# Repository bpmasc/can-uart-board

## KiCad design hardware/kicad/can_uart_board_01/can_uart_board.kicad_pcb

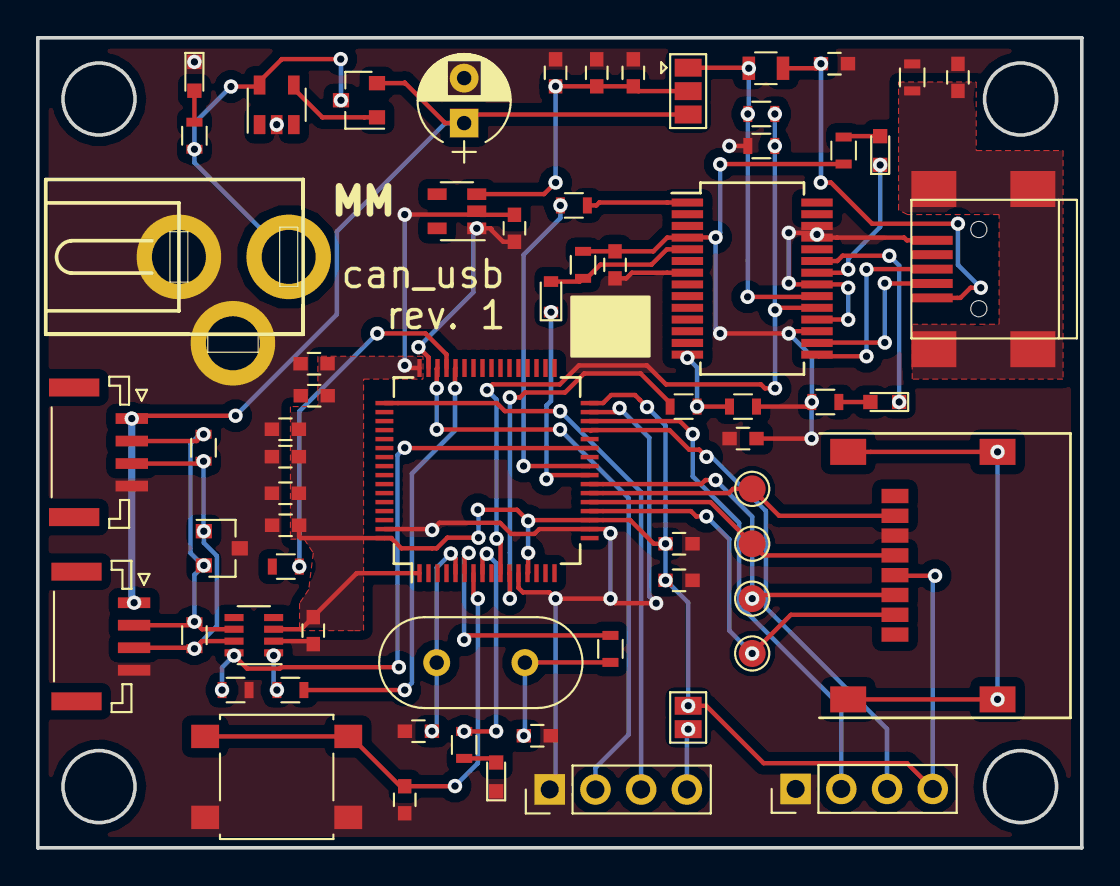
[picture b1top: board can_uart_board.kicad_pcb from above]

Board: 2 copper layers, 58.0 x 45.0 mm, 66 parts (0 on the bottom side), 46 nets.

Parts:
C10, C11: C; C_0603
C12, C13, C15, C40: 0.1u; C_0603
C14, C16, C28, C200: 4.7u; C_0603
C17: 0.01u; C_0603
C19: CP; CP_Radial_D5.0mm_P2.50mm
C20, C25, C26, C27, C29, C201: 100n; C_0603
C23, C24: 20p; C_0603
C202: 1u; C_0603
D10: D_Zener; D_0603
D11, D12, D13, D20: LED; LED_0603
D40: NUP2105L; SOT-23
FB0: Ferrite_Bead; L_0805
J11: USB_B_Mini; USB_Mini-B
J12: Barrel_Jack_Switch; con-jack-DCJ0303
J20, J21: Conn_01x04_Male; Pin_Header_Straight_1x04_Pitch2.54mm
J30: Micro_SD_Card_Det; MicroSd_Wurth_693072010801
J40, J41: Conn_01x04_Male; JST_GH_SM04B-GHS-TB_04x1.25mm_Angled
JP0: Jumper_2_Open; SolderJumper-2_P1.3mm_Open_Pad1.0x1.5mm
JP10: Jumper_3_Open; SolderJumper-3_P1.3mm_Open_Pad1.0x1.5mm
Q10: CPH3462_SOT23_3; SOT-23
R10: 1M; R_0603
R11: 4k7; R_0603
R12, R14, R17, R18: 10k; R_0603
R13, R26, R27, R42, R43: 0; R_0603
R15, R16, R19, R40, R44: 120; R_0603
R41: R; R_0603
SW20: SW_Push_Dual; SW_SPST_B3S-1000
TP30, TP31, TP32, TP33: TestPoint; TestPoint_Pad_D1.5mm
U10: FT232RL; SSOP-28_5.3x10.2mm_Pitch0.65mm
U11: TLV1117_33_SOT223; SOT-23-5
U13: TPS2400_SOT23_5; SOT-23-5
U40: MAX3051; SOT-23-8
U^20: STM32F091RBTx; LQFP-64_10x10mm_Pitch0.5mm
Y20: Crystal; Crystal_HC18-U_Vertical

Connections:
+3V3: C11.1, C25.1, C26.1, C27.1, C28.1, C29.1, C40.1, C200.1, C201.1, C202.1, J21.4, J30.4, JP0.1, U11.2, U40.3, U^20.1, U^20.13, U^20.19, U^20.32, U^20.48, U^20.64
/if_can/CAN_H: D40.1, J40.3, J41.3, R40.1, R44.1, U40.7
/if_can/CAN_L: D40.2, J40.2, J41.2, R40.2, R44.2, U40.6
/if_can/CAN_RS: R41.1, U40.8, U^20.27
/if_can/CAN_RX: R43.2, U^20.45
/if_can/CAN_TX: R42.2, U^20.44
/if_openlog/uSD_CS: J30.2, TP30.1, U^20.20
/if_openlog/uSD_MISO: J30.7, TP33.1, U^20.22
/if_openlog/uSD_MOSI: J30.3, TP31.1, U^20.23
/if_openlog/uSD_SCK: J30.5, TP32.1, U^20.21
/if_uart_power/CONV_N_USB: R18.2, U^20.11
/if_uart_power/FT232_3V3: C13.1, C14.1, R14.1, R15.1, R16.1, R17.1, U10.4, U10.17
/if_uart_power/FT232_DM: J11.2, U10.16
/if_uart_power/FT232_DP: J11.3, U10.15
/if_uart_power/UART_N_RESET: R11.2, R12.1, U10.19, U^20.10
/if_uart_power/UART_PW_EN: R17.2, R18.1, U10.14
/if_uart_power/UART_RX: R13.1, U^20.25
/if_uart_power/UART_RXLED: D12.1, U10.23
/if_uart_power/UART_TX: D10.1, U^20.24
/if_uart_power/UART_TXLED: D11.1, U10.22
/if_uart_power/USB_UART_VBUS: FB0.1, JP10.1, R11.1, U10.20
/if_uart_power/V_JUMPER: C10.1, C15.1, C16.1, JP10.2, U11.3
/uC/EXT_SCL: J21.3, U^20.29
/uC/EXT_SDA: J21.2, U^20.30
/uC/LED: R27.2, U^20.8
/uC/OSC_IN: C23.1, U^20.5, Y20.1
/uC/OSC_OUT: R26.1, U^20.6
/uC/SWCLK: J20.3, U^20.49
/uC/SWDIO: J20.2, U^20.46
/uC/nRESET: C20.1, SW20.2, U^20.7
GND: C10.2, C11.2, C12.2, C13.2, C14.2, C15.2, C16.2, C17.2, C19.2, C20.2, C23.2, C24.2, C25.2, C26.2, C27.2, C28.2, C29.2, C40.2, C200.2, C201.2, C202.2, D13.1, D20.1, D40.3, J11.5, J12.2, J12.3, J20.1, J21.1, J30.6, J40.4, J41.4, R10.2, R12.2, R41.2, SW20.1, U10.7, U10.18, U10.21, U10.25, U10.26, U11.1, U13.2, U40.2, U^20.12, U^20.18, U^20.31, U^20.47, U^20.63
unnamed: C12.1, J11.6, R10.1
unnamed: C17.1, FB0.2, J11.1
unnamed: C24.1, R26.2, Y20.2
unnamed: D10.2, R14.2, U10.5
unnamed: D11.2, R15.2
unnamed: D12.2, R16.2
unnamed: D13.2, R19.2
unnamed: D20.2, R27.1
unnamed: J12.1, Q10.3, R19.1, U13.5
unnamed: J20.4, JP0.2
unnamed: Q10.1, U13.4
unnamed: R13.2, U10.1
unnamed: R42.1, U40.1
unnamed: R43.1, U40.4
VBUS: C19.1, J40.1, J41.1, JP10.3, Q10.2

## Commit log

2019-03-31 Added first version of pcb
2020-02-16 added rev 1
